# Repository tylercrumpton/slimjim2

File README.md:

# slimjim2

**slimjim2** is a multi-purpose adapter board for RF form-factor Synapse Wireless SNAP modules like the RF100 and RF200.
The original [slimjim] supported a custom module dubbed the TC200, but the **slimjim2** drops support for it in favor of
a ton of cool features. All pins are broken out to a set of standard 0.1" (2.54 mm) headers for jumper cables,
breadboarding, or soldering.

## Features
**slimjim2** contains a few features that make using RF-style SNAP devices in one-off or development projects easier:

- 0.1" (2.54 mm) pin header breakout for all pins
- Silkscreen marks for pins
- Optionally-populated functionality:
  - 3.3V regulator capable of handling input voltages of up tp 15V
  - CH430 USB<->UART adapter for SNAP bridge applications
  - Auto-reset on DTR (for SNAP bridge applications)
  - Reset pushbutton
  - 6-pin serial header
  - Backfeed protection diode for USB power
- USB Type-C port can be used for serial data and power (if regulator and USB<->UART populated)
- 3mm mounting hole
- Module orientation marker
- Open-source hardware designs

## Specifications:
- Dimensions: 1.9" x 1.4" (48.26mm x 35.56mm)

## Supported boards
The following modules should work in the **slimjim2**:

- RF100
- RF200
- RF220
- RF300

## Versions

### v2.1

- USB Type-C connector
- Backfeed protection diode for USB power
- Flat reset button (not side-mounted)
 
### v2.0
 
- MicroUSB connector
- Side-mounted reset button

[slimjim]: https://github.com/tylercrumpton/slimjim

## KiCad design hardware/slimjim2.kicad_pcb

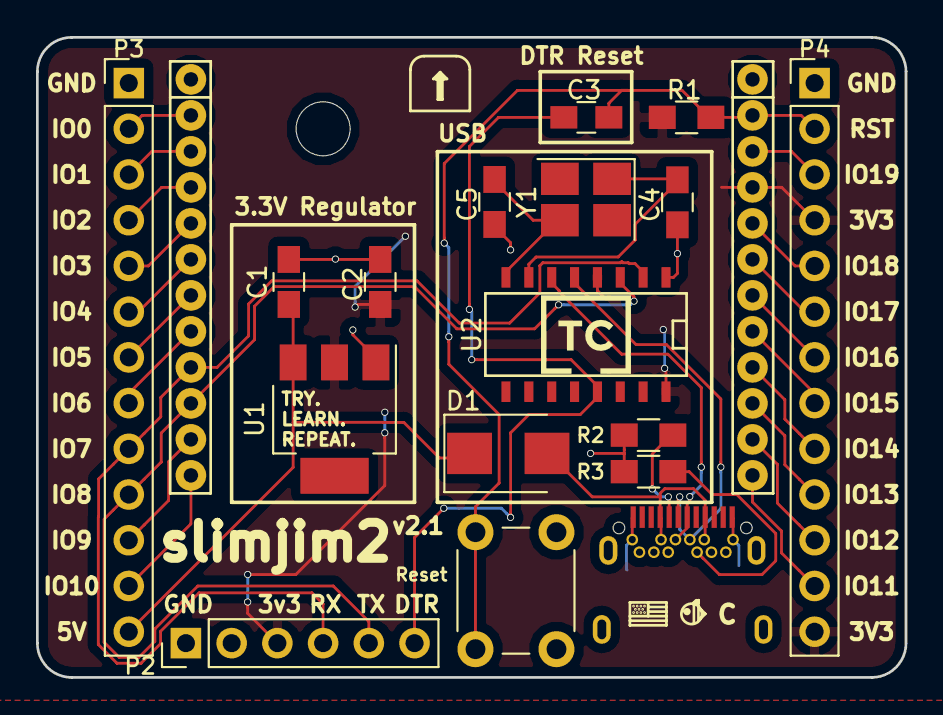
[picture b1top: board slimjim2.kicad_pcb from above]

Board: 2 copper layers, 48.3 x 35.6 mm, 19 parts (0 on the bottom side), 32 nets.

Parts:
C1, C2: 10u; C_0805_HandSoldering
C3: 0.1u; C_0805_HandSoldering
C4, C5: 22p; C_0805_HandSoldering
D1: 1N5824; D_SMB
J1: USB_C_Receptacle_USB2.0; USB_C_Receptacle_SMD_THT
P2: CONN_01X06; Pin_Header_Straight_1x06_Pitch2.54mm
P3, P4: CONN_01X13; Pin_Header_Straight_1x13_Pitch2.54mm
R1: 10k; R_0805_HandSoldering
R2, R3: 5.1k; R_0805_HandSoldering
Reset: RESET_SW; SW_PUSH_6mm_h4.3mm
U1: AMS1117-3.3; SOT-223
U2: CH340G; SO-16-N
U3: RF200
Y1: 12MHz; Crystal_SMD_3225-4pin_3.2x2.5mm_HandSoldering
svg2mod: G***; tc_30mm

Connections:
3V3: C2.1, P2.3, P4.4, P4.13, R1.1, U1.2, U2.4, U2.16, U3.21
5V: C1.1, D1.1, P3.13, U1.3
DTR: C3.2, P2.6, U2.13
GND: C1.2, C2.2, C4.2, C5.2, J1.A1, J1.A12, J1.B1, J1.B12, P2.1, P3.1, P4.1, R2.1, R3.1, Reset.2, U1.1, U2.1, U3.1, U3.24
GPIO0: P3.2, U3.2
GPIO1: P3.3, U3.3
GPIO2: P3.4, U3.4
GPIO3: P3.5, U3.5
GPIO4: P3.6, U3.6
GPIO5: P3.7, U3.7
GPIO6: P3.8, U3.8
GPIO9: P3.11, U3.11
GPIO10: P3.12, U3.12
GPIO11: P4.12, U3.13
GPIO12: P4.11, U3.14
GPIO13: P4.10, U3.15
GPIO14: P4.9, U3.16
GPIO15: P4.8, U3.17
GPIO16: P4.7, U3.18
GPIO17: P4.6, U3.19
GPIO18: P4.5, U3.20
GPIO19: P4.3, U3.22
unnamed: D1.2, J1.A4, J1.A9, J1.B4, J1.B9
unnamed: J1.A5, R2.2
unnamed: J1.A6, J1.B6, U2.5
unnamed: J1.A7, J1.B7, U2.6
unnamed: J1.B5, R3.2
SNAP_RST: C3.1, P4.2, R1.2, Reset.1, U3.23
SNAP_RXD1: P2.4, P3.9, U2.2, U3.9
SNAP_TXD1: P2.5, P3.10, U2.3, U3.10
XI: C4.1, U2.7, Y1.1
XO: C5.1, U2.8, Y1.3

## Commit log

2017-09-21 Set up initial project structure for sb_ch340g.
2017-09-22 Schematic capture and basic board layout.
2017-09-24 Cleanup layout.
2017-09-24 First pass at routing.
2017-10-03 Move everything to reflect snapcap name.
2017-10-03 Fix submodules.
2017-10-03 Start adding silk.
2017-10-05 Finish up silk.
2017-10-05 Add README.
2017-10-05 Add images and dimensions.
2017-10-11 Add output settings.
2018-11-09 Update for KiCad5.
2018-11-12 Update PCB with USB-C part.
2018-11-12 Final board cleanup.
2018-11-13 Update version info.
2018-11-13 Update README for v2.1.

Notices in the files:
hardware/slimjim2.kicad_pcb:
CC-BY-SA 4.0
